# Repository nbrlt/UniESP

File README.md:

# UniESP
This is a simple board to control 2 unipolar stepper motors. It is meant to control a telescope mount using OnStepX on the ESP32. 

It relies on an ESP32 dev board with 30 pins and a RP2040 in the form of the Raspberry pico zero from waveshare as the driver logic. 

The code for OnStepX is found here: https://github.com/nbrlt/OnStepX (for now).
## The RP2040
The RP2040 is used to convert the StepDir interface of OnStepX to a 4 pin control for the DRV8932. I used that specific bridge driver to have a current control on the stepper (I could not find any StepDir bridge with proper current control).

The code for the Raspberry pico zero can be found here: [https://github.com/nbrlt/RP2040_Unipolar_StepDir_Driver](https://github.com/nbrlt/RP2040_StepDirToPWM_StepperLogic)

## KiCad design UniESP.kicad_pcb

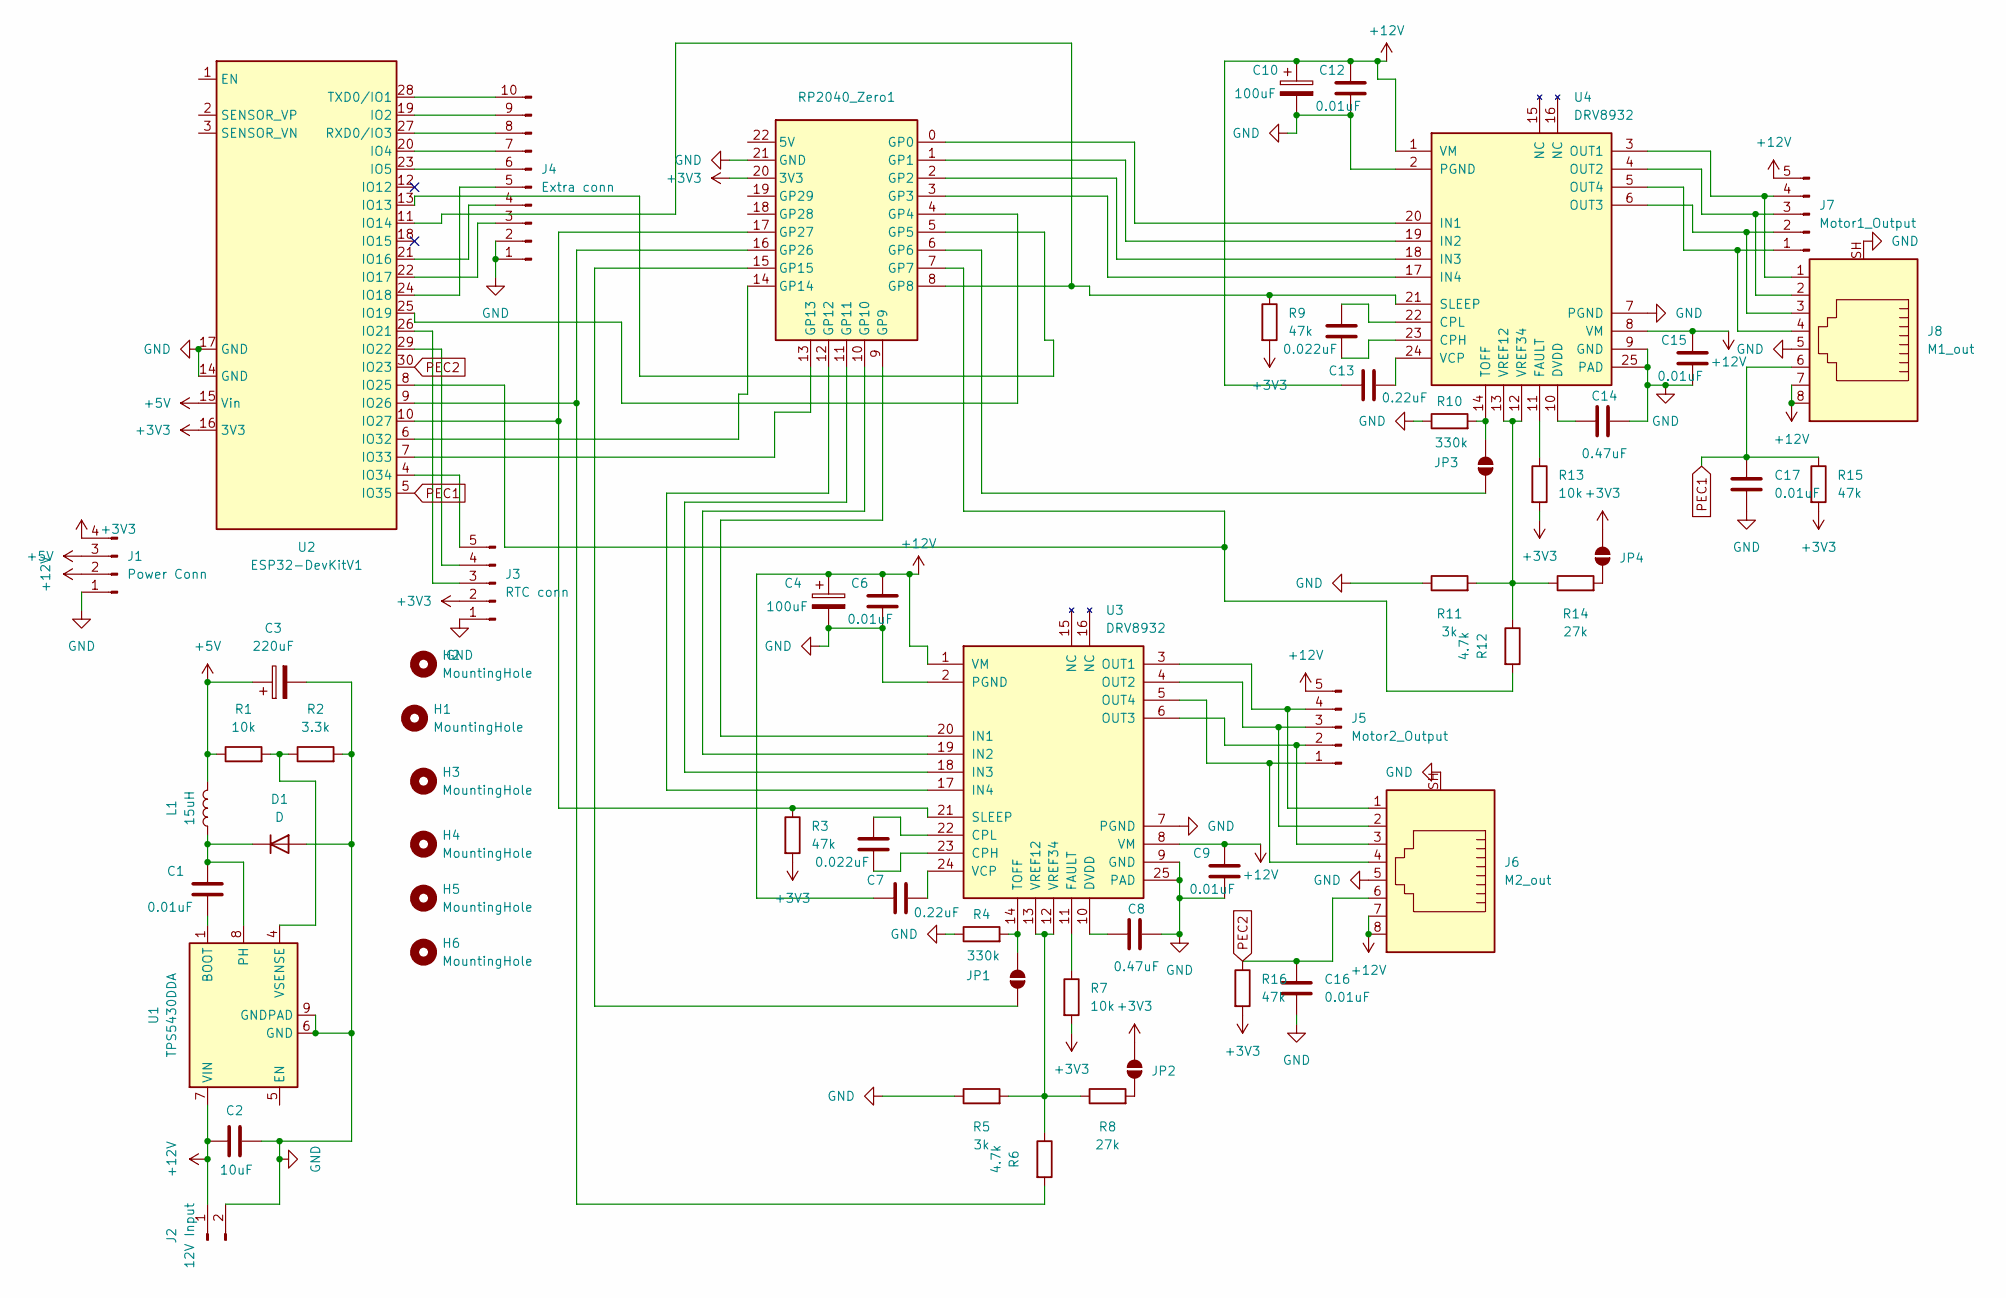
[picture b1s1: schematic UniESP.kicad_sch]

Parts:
C1, C6, C9, C12, C15, C16, C17: 0.01uF; C_0402_1005Metric
C2: 10uF; C_0603_1608Metric
C3: 220uF; CP_Radial_D6.3mm_P2.50mm
C4, C10: 100uF; CP_Radial_D6.3mm_P2.50mm
C5, C11: 0.022uF; C_0402_1005Metric
C7, C13: 0.22uF; C_0603_1608Metric
C8, C14: 0.47uF; C_0603_1608Metric
D1: D; D_SMA; LCSC C14996
H1, H2, H3, H6: MountingHole; JLCPCB_MountingHole
H4, H5: MountingHole; MountingHole_2.2mm_M2
J1: Power Conn; PinHeader_1x04_P2.54mm_Vertical
J2: 12V Input; JST_NV_B02P-NV_1x02_P5.00mm_Vertical
J3: RTC conn; PinHeader_1x05_P2.54mm_Vertical
J4: Extra conn; PinSocket_1x10_P2.54mm_Vertical
J5: Motor2_Output; JST_XH_B5B-XH-A_1x05_P2.50mm_Vertical
J6: M2_out; RJ45_HALO_HFJ11-x2450HRL_Horizontal
J7: Motor1_Output; JST_XH_B5B-XH-A_1x05_P2.50mm_Vertical
J8: M1_out; RJ45_HALO_HFJ11-x2450HRL_Horizontal
JP1: M2_Toff_MCU; SolderJumper-2_P1.3mm_Open_TrianglePad1.0x1.5mm
JP2: M2_Vref_5V; SolderJumper-2_P1.3mm_Open_TrianglePad1.0x1.5mm
JP3: M1_Toff_MCU; SolderJumper-2_P1.3mm_Open_TrianglePad1.0x1.5mm
JP4: M1_Vref_5V; SolderJumper-2_P1.3mm_Open_TrianglePad1.0x1.5mm
L1: 15uH; L_Changjiang_FNR5040S; LCSC C167969
R1, R7, R13: 10k; R_0603_1608Metric
R2: 3.3k; R_0603_1608Metric
R3, R9, R15, R16: 47k; R_0603_1608Metric
R4, R10: 330k; R_0603_1608Metric
R5, R11: 3k; R_0603_1608Metric
R6, R12: 4.7k; R_0603_1608Metric
R8, R14: 27k; R_0603_1608Metric
RP2040_Zero1: WS_Pico_Zero_header
U1: TPS5430DDA; TI_SO-PowerPAD-8_ThermalVias; LCSC C9864
U2: ESP32-DevKitV1
U3, U4: DRV8932; VQFN-24-1EP_4x4mm_P0.5mm_EP2.45x2.45mm_BIGThermalVias; LCSC C2876703

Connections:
+3V3: J1.4, J3.2, JP2.2 (B), JP4.2 (B), R3.2, R7.2, R9.2, R13.2, R15.2, R16.2, RP2040_Zero1.20 (3V3), U2.16 (3V3)
+5V: C3.1, J1.3, L1.2, R1.1, U2.15 (Vin)
+12V: C2.1, C4.1, C6.1, C7.2, C9.1, C10.1, C12.1, C13.2, C15.1, J1.2, J2.1, J5.5, J6.7, J6.8, J7.5, J8.7, J8.8, U1.7 (VIN), U3.1 (VM), U3.8 (VM), U4.1 (VM), U4.8 (VM)
GND: C2.2, C3.2, C4.2, C6.2, C8.2, C9.2, C10.2, C12.2, C14.2, C15.2, C16.2, C17.2, D1.2 (A), J1.1, J2.2, J3.1, J4.1, J4.2, J6.5, J6.SH, J8.5, J8.SH, R2.2, R4.1, R5.1, R10.1, R11.1, RP2040_Zero1.21 (GND), U1.6 (GND), U1.9 (GNDPAD), U2.14 (GND), U2.17 (GND), U3.2 (PGND), U3.7 (PGND), U3.9 (GND), U3.25 (PAD), U4.2 (PGND), U4.7 (PGND), U4.9 (GND), U4.25 (PAD)
unnamed: C1.1, D1.1 (K), L1.1, U1.8 (PH)
unnamed: J3.3, U2.26 (IO21)
unnamed: J3.4, U2.29 (IO22)
unnamed: J3.5, U2.4 (IO34)
unnamed: J4.3, U2.22 (IO17)
unnamed: J4.4, U2.21 (IO16)
unnamed: J4.5, U2.24 (IO18)
unnamed: J4.6, U2.23 (IO5)
unnamed: J4.7, U2.20 (IO4)
unnamed: J4.8, U2.27 (RXD0/IO3)
unnamed: J4.9, U2.19 (IO2)
unnamed: J4.10, U2.28 (TXD0/IO1)
unnamed: J5.1, J6.4, U3.5 (OUT4)
unnamed: J5.2, J6.3, U3.6 (OUT3)
unnamed: J5.3, J6.2, U3.4 (OUT2)
unnamed: J5.4, J6.1, U3.3 (OUT1)
unnamed: J7.1, J8.4, U4.5 (OUT4)
unnamed: J7.2, J8.3, U4.6 (OUT3)
unnamed: J7.3, J8.2, U4.4 (OUT2)
unnamed: J7.4, J8.1, U4.3 (OUT1)
unnamed: JP1.1 (A), RP2040_Zero1.15 (GP15)
unnamed: JP1.2 (B), R4.2, U3.14 (TOFF)
unnamed: JP2.1 (A), R8.2
unnamed: JP3.1 (A), RP2040_Zero1.6 (GP6)
unnamed: JP3.2 (B), R10.2, U4.14 (TOFF)
unnamed: JP4.1 (A), R14.2
unnamed: RP2040_Zero1.0 (GP0), U4.20 (IN1)
unnamed: RP2040_Zero1.1 (GP1), U4.19 (IN2)
unnamed: RP2040_Zero1.2 (GP2), U4.18 (IN3)
unnamed: RP2040_Zero1.3 (GP3), U4.17 (IN4)
unnamed: RP2040_Zero1.4 (GP4), U2.25 (IO19)
unnamed: RP2040_Zero1.5 (GP5), U2.13 (IO13)
unnamed: R12.2, RP2040_Zero1.7 (GP7), U2.8 (IO25)
unnamed: R9.1, RP2040_Zero1.8 (GP8), U2.11 (IO14), U4.21 (SLEEP)
unnamed: RP2040_Zero1.9 (GP9), U3.20 (IN1)
unnamed: RP2040_Zero1.10 (GP10), U3.19 (IN2)
unnamed: RP2040_Zero1.11 (GP11), U3.18 (IN3)
unnamed: RP2040_Zero1.12 (GP12), U3.17 (IN4)
unnamed: RP2040_Zero1.13 (GP13), U2.7 (IO33)
unnamed: RP2040_Zero1.14 (GP14), U2.6 (IO32)
unnamed: R6.2, RP2040_Zero1.16 (GP26), U2.9 (IO26)
unnamed: R3.1, RP2040_Zero1.17 (GP27), U2.10 (IO27), U3.21 (SLEEP)
unnamed: C1.2, U1.1 (BOOT)
unnamed: R1.2, R2.1, U1.4 (VSENSE)
unnamed: C5.2, U3.23 (CPH)
unnamed: C5.1, U3.22 (CPL)
unnamed: C8.1, U3.10 (DVDD)
unnamed: R7.1, U3.11 (FAULT)
unnamed: C7.1, U3.24 (VCP)
unnamed: R5.2, R6.1, R8.1, U3.12 (VREF34), U3.13 (VREF12)
unnamed: C11.2, U4.23 (CPH)
unnamed: C11.1, U4.22 (CPL)
unnamed: C14.1, U4.10 (DVDD)
unnamed: R13.1, U4.11 (FAULT)
unnamed: C13.1, U4.24 (VCP)
unnamed: R11.2, R12.1, R14.1, U4.12 (VREF34), U4.13 (VREF12)
PEC1: C17.1, J8.6, R15.1, U2.5 (IO35)
PEC2: C16.1, J6.6, R16.1, U2.30 (IO23)

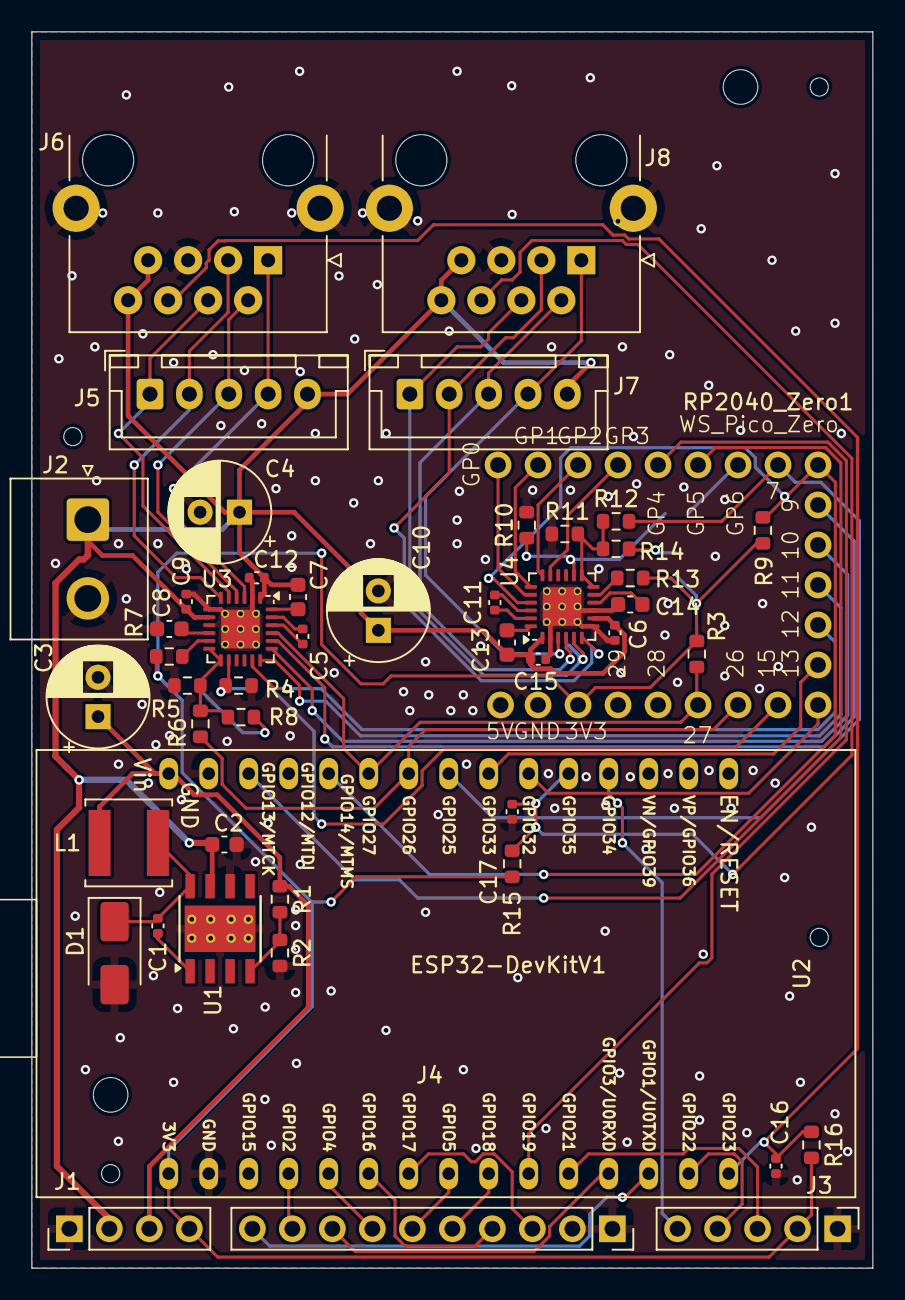
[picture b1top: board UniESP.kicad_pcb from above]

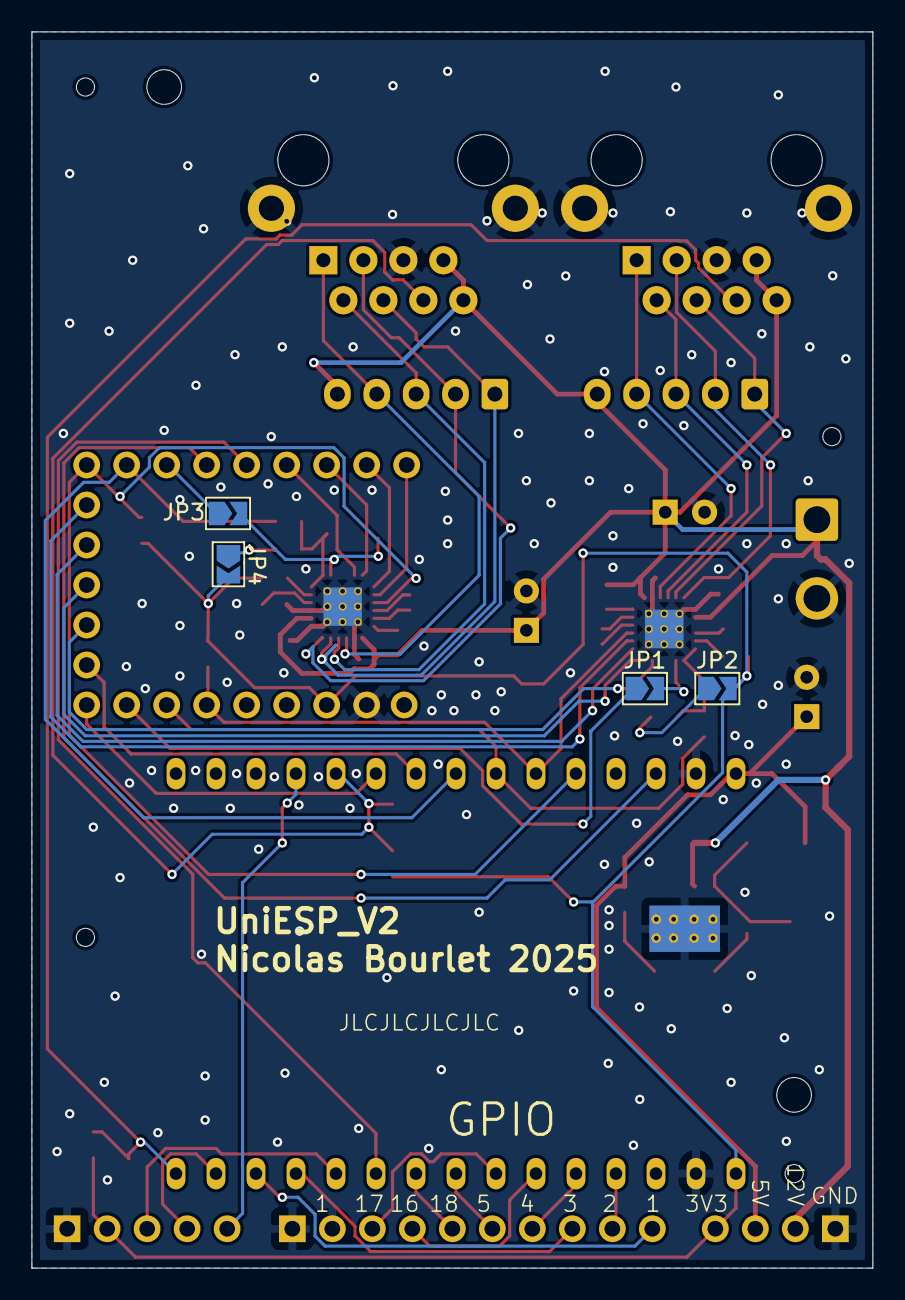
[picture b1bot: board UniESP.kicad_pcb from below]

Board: 2 copper layers, 53.4 x 78.5 mm, 58 parts (4 on the bottom side), 62 nets.

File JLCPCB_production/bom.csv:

Designator,Footprint,Quantity,Value,LCSC Part #
"C1, C16, C17",0402,3,0.01uF,
"C10, C4",CP_Radial_D6.3mm_P2.50mm,2,100uF,
"C11, C5",0402,2,0.022uF,
"C12, C15, C6, C9",0402,4,0.01uF,
"C13, C7",0603,2,0.22uF,
"C14, C8",0603,2,0.47uF,
C2,0603,1,10uF,
C3,CP_Radial_D6.3mm_P2.50mm,1,220uF,
D1,D_SMA,1,D,C14996
J1,PinHeader_1x04_P2.54mm_Vertical,1,Power Conn,
J2,JST_NV_B02P-NV_1x02_P5.00mm_Vertical,1,12V Input,
J3,PinHeader_1x05_P2.54mm_Vertical,1,RTC conn,
J4,PinSocket_1x10_P2.54mm_Vertical,1,Extra conn,
J5,JST_XH_B5B-XH-A_1x05_P2.50mm_Vertical,1,Motor2_Output,
J6,RJ45_HALO_HFJ11-x2450HRL_Horizontal,1,M2_out,
J7,JST_XH_B5B-XH-A_1x05_P2.50mm_Vertical,1,Motor1_Output,
J8,RJ45_HALO_HFJ11-x2450HRL_Horizontal,1,M1_out,
L1,L_Changjiang_FNR5040S,1,15uH,C167969
R1,0603,1,10k,
"R10, R4",0603,2,330k,
"R11, R5",0603,2,3k,
"R12, R6",0603,2,4.7k,
"R13, R7",0603,2,10k,
"R14, R8",0603,2,27k,
"R15, R16, R3, R9",0603,4,47k,
R2,0603,1,3.3k,
RP2040_Zero1,WS_Pico_Zero_header,1,~,
U1,TI_SO-PowerPAD-8_ThermalVias,1,TPS5430DDA,C9864
U2,ESP32-DevKitV1,1,ESP32-DevKitV1,
"U3, U4",VQFN-24-1EP_4x4mm_P0.5mm_EP2.45x2.45mm_BIGThermalVias,2,DRV8932,C2876703

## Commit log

2025-05-04 Added PEC filtering
